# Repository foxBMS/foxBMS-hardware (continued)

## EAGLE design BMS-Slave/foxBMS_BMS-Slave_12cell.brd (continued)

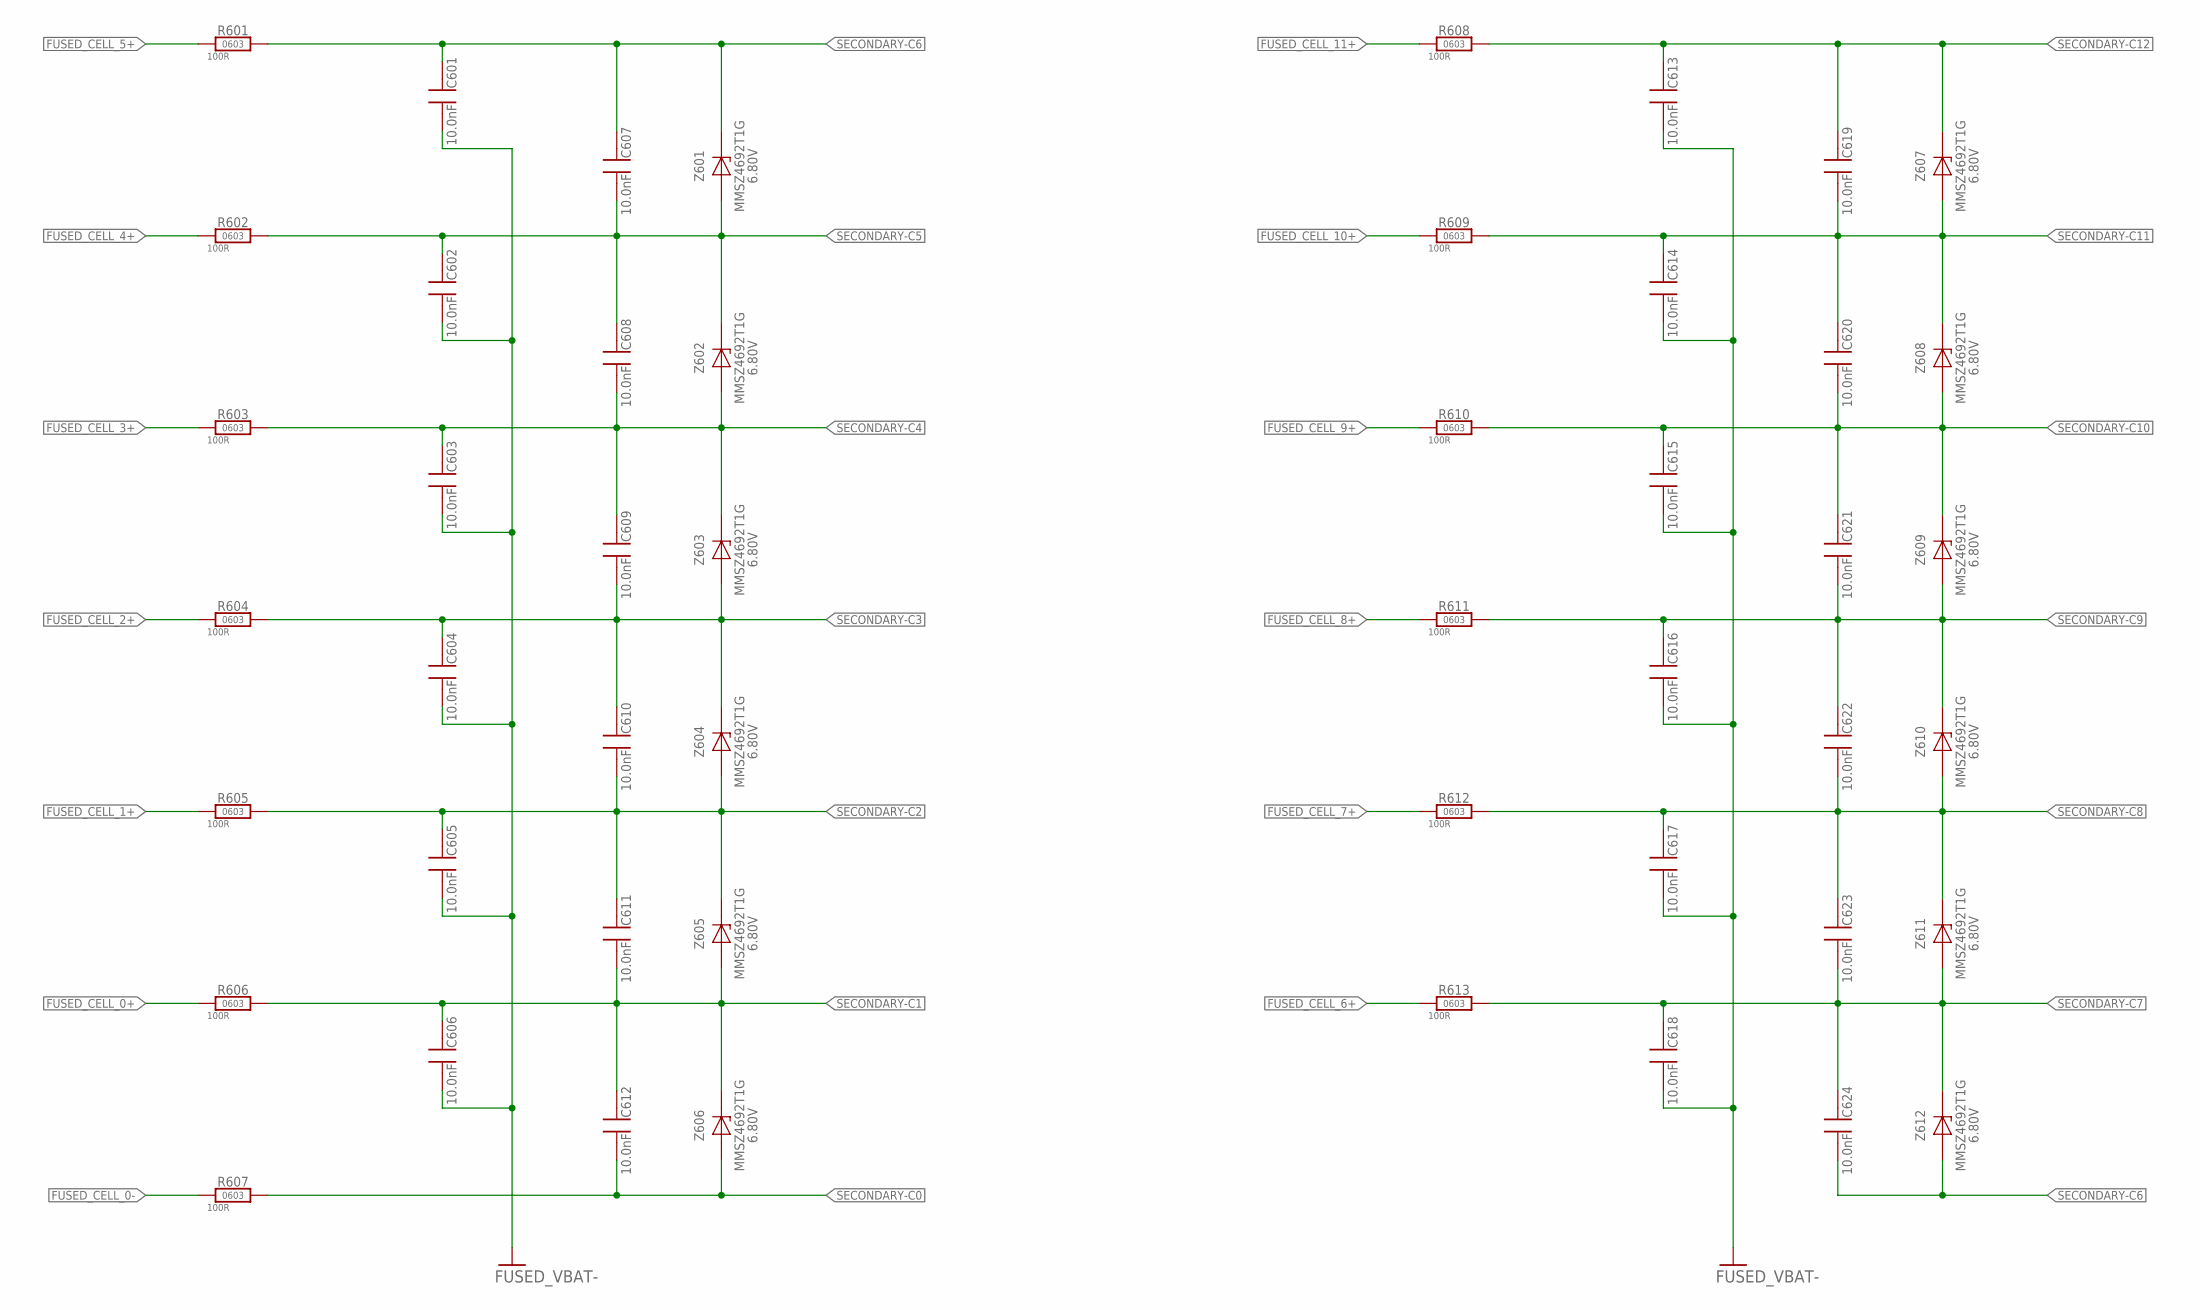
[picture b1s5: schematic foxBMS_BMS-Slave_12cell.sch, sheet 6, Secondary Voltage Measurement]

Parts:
C601, C602, C603, C604, C605, C606, C607, C608, C609, C610, C611, C612, C613, C614, C615, C616, C617, C618, C619, C620, C621, C622, C623, C624: 10nF, 100V, 10%; C_SMD_0603_(1608)_R_KEMET_REV01
R601, R602, R603, R604, R605, R606, R607, R608, R609, R610, R611, R612, R613: 100R_0603_R_VISHAY_1%_TK100_REV_01; R_SMD_0603_R_VISHAY_REV01
Z601, Z602, Z603, Z604, Z605, Z606, Z607, Z608, Z609, Z610, Z611, Z612: 6.8V, 500mW; D_SMD_SOD-123_R_ON_REV01

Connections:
FUSED_CELL_0+: R606.1; also elsewhere on the board
FUSED_CELL_0-: R607.1; also elsewhere on the board
FUSED_CELL_1+: R605.1; also elsewhere on the board
FUSED_CELL_2+: R604.1; also elsewhere on the board
FUSED_CELL_3+: R603.1; also elsewhere on the board
FUSED_CELL_4+: R602.1; also elsewhere on the board
FUSED_CELL_5+: R601.1; also elsewhere on the board
FUSED_CELL_6+: R613.1; also elsewhere on the board
FUSED_CELL_7+: R612.1; also elsewhere on the board
FUSED_CELL_8+: R611.1; also elsewhere on the board
FUSED_CELL_9+: R610.1; also elsewhere on the board
FUSED_CELL_10+: R609.1; also elsewhere on the board
FUSED_CELL_11+: R608.1; also elsewhere on the board
FUSED_VBAT-: C601.2, C602.2, C603.2, C604.2, C605.2, C606.2, C613.2, C614.2, C615.2, C616.2, C617.2, C618.2; also elsewhere on the board
SECONDARY-C0: C612.2, R607.2, Z606.A; also elsewhere on the board
SECONDARY-C1: C606.1, C611.2, C612.1, R606.2, Z605.A, Z606.K (C); also elsewhere on the board
SECONDARY-C2: C605.1, C610.2, C611.1, R605.2, Z604.A, Z605.K (C); also elsewhere on the board
SECONDARY-C3: C604.1, C609.2, C610.1, R604.2, Z603.A, Z604.K (C); also elsewhere on the board
SECONDARY-C4: C603.1, C608.2, C609.1, R603.2, Z602.A, Z603.K (C); also elsewhere on the board
SECONDARY-C5: C602.1, C607.2, C608.1, R602.2, Z601.A, Z602.K (C); also elsewhere on the board
SECONDARY-C6: C601.1, C607.1, C624.2, R601.2, Z601.K (C), Z612.A; also elsewhere on the board
SECONDARY-C7: C618.1, C623.2, C624.1, R613.2, Z611.A, Z612.K (C); also elsewhere on the board
SECONDARY-C8: C617.1, C622.2, C623.1, R612.2, Z610.A, Z611.K (C); also elsewhere on the board
SECONDARY-C9: C616.1, C621.2, C622.1, R611.2, Z609.A, Z610.K (C); also elsewhere on the board
SECONDARY-C10: C615.1, C620.2, C621.1, R610.2, Z608.A, Z609.K (C); also elsewhere on the board
SECONDARY-C11: C614.1, C619.2, C620.1, R609.2, Z607.A, Z608.K (C); also elsewhere on the board
SECONDARY-C12: C613.1, C619.1, R608.2, Z607.K (C); also elsewhere on the board

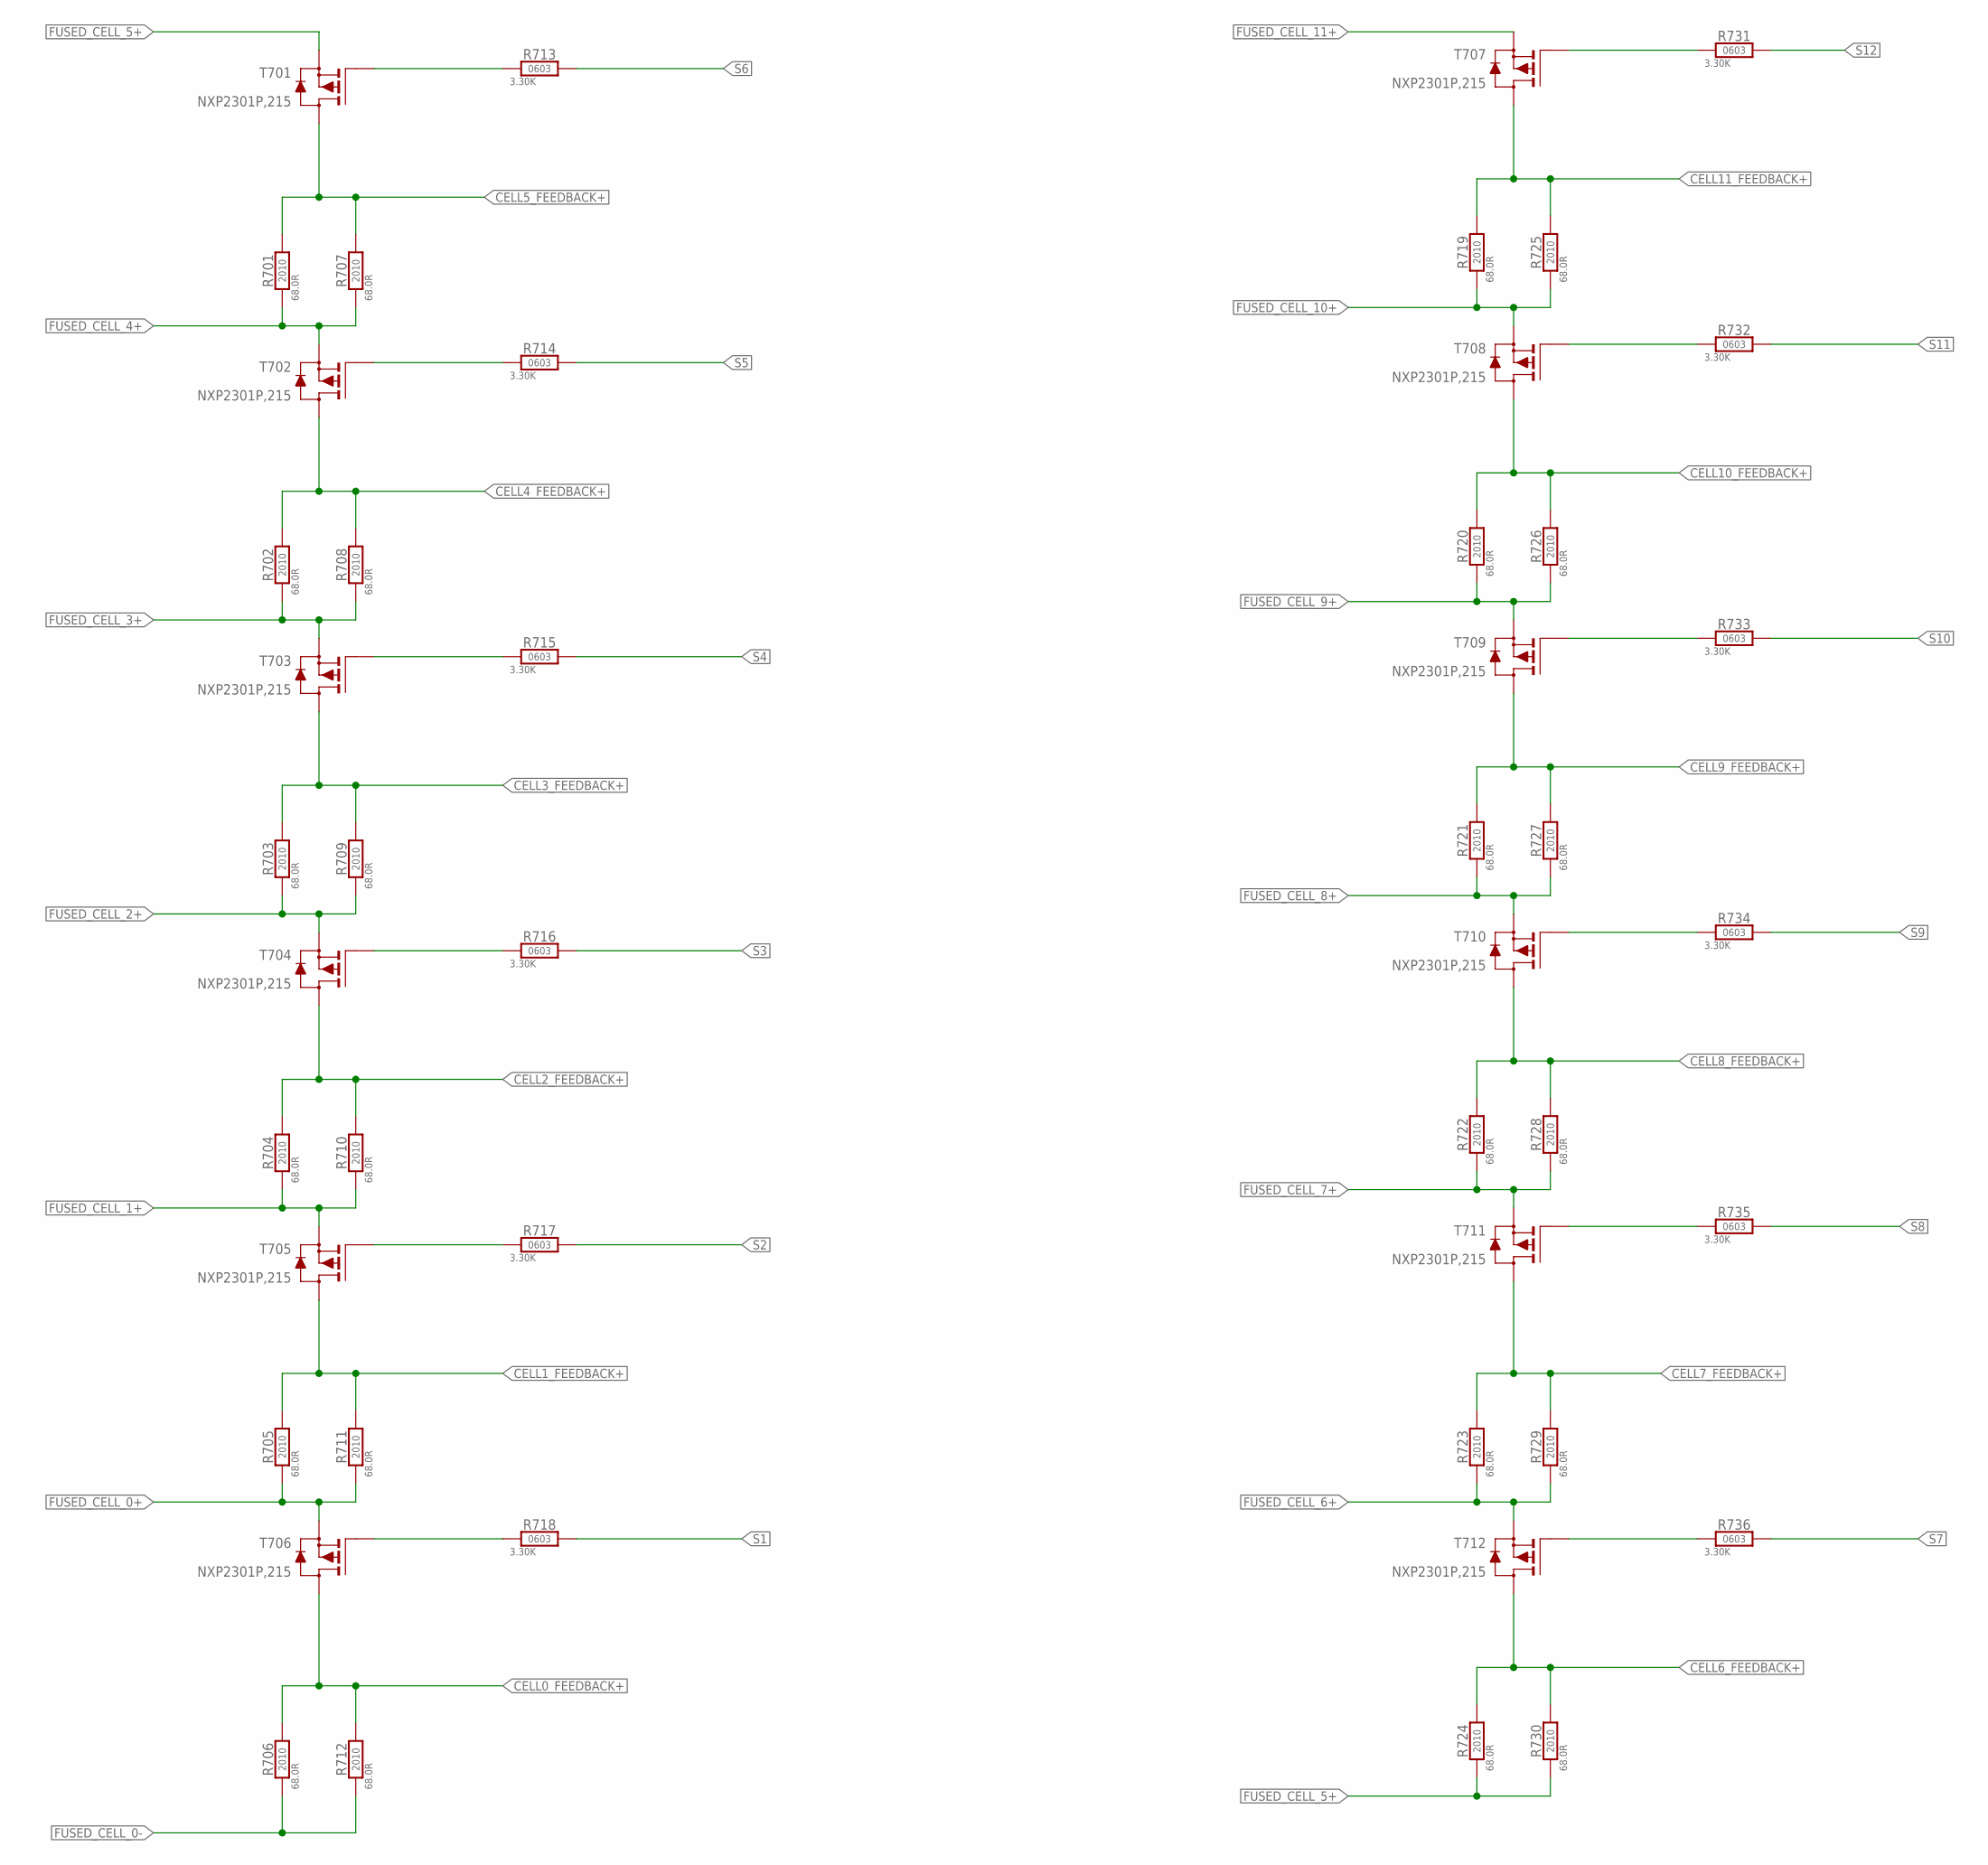
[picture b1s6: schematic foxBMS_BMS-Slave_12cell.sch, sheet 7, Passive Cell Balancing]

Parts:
R701, R702, R703, R704, R705, R706, R707, R708, R709, R710, R711, R712, R719, R720, R721, R722, R723, R724, R725, R726, R727, R728, R729, R730: 72R, 1%; R_SMD_2010_R_YAGEO_REV01
R713, R714, R715, R716, R717, R718, R731, R732, R733, R734, R735, R736: 3.3k, 10%, 1/10W; R_SMD_0603_R_VISHAY_REV01
T701, T702, T703, T704, T705, T706, T707, T708, T709, T710, T711, T712: NX2301P; D_SMD_SOT23_(TO-236AB)_R_NXP_REV01

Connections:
CELL0_FEEDBACK+: R706.P$2 (2), R712.P$2 (2), T706.3 (D); also elsewhere on the board
CELL1_FEEDBACK+: R705.P$2 (2), R711.P$2 (2), T705.3 (D); also elsewhere on the board
CELL2_FEEDBACK+: R704.P$2 (2), R710.P$2 (2), T704.3 (D); also elsewhere on the board
CELL3_FEEDBACK+: R703.P$2 (2), R709.P$2 (2), T703.3 (D); also elsewhere on the board
CELL4_FEEDBACK+: R702.P$2 (2), R708.P$2 (2), T702.3 (D); also elsewhere on the board
CELL5_FEEDBACK+: R701.P$2 (2), R707.P$2 (2), T701.3 (D); also elsewhere on the board
CELL6_FEEDBACK+: R724.P$2 (2), R730.P$2 (2), T712.3 (D); also elsewhere on the board
CELL7_FEEDBACK+: R723.P$2 (2), R729.P$2 (2), T711.3 (D); also elsewhere on the board
CELL8_FEEDBACK+: R722.P$2 (2), R728.P$2 (2), T710.3 (D); also elsewhere on the board
CELL9_FEEDBACK+: R721.P$2 (2), R727.P$2 (2), T709.3 (D); also elsewhere on the board
CELL10_FEEDBACK+: R720.P$2 (2), R726.P$2 (2), T708.3 (D); also elsewhere on the board
CELL11_FEEDBACK+: R719.P$2 (2), R725.P$2 (2), T707.3 (D); also elsewhere on the board
FUSED_CELL_0+: R705.P$1 (1), R711.P$1 (1), T706.2 (S); also elsewhere on the board
FUSED_CELL_0-: R706.P$1 (1), R712.P$1 (1); also elsewhere on the board
FUSED_CELL_1+: R704.P$1 (1), R710.P$1 (1), T705.2 (S); also elsewhere on the board
FUSED_CELL_2+: R703.P$1 (1), R709.P$1 (1), T704.2 (S); also elsewhere on the board
FUSED_CELL_3+: R702.P$1 (1), R708.P$1 (1), T703.2 (S); also elsewhere on the board
FUSED_CELL_4+: R701.P$1 (1), R707.P$1 (1), T702.2 (S); also elsewhere on the board
FUSED_CELL_5+: R724.P$1 (1), R730.P$1 (1), T701.2 (S); also elsewhere on the board
FUSED_CELL_6+: R723.P$1 (1), R729.P$1 (1), T712.2 (S); also elsewhere on the board
FUSED_CELL_7+: R722.P$1 (1), R728.P$1 (1), T711.2 (S); also elsewhere on the board
FUSED_CELL_8+: R721.P$1 (1), R727.P$1 (1), T710.2 (S); also elsewhere on the board
FUSED_CELL_9+: R720.P$1 (1), R726.P$1 (1), T709.2 (S); also elsewhere on the board
FUSED_CELL_10+: R719.P$1 (1), R725.P$1 (1), T708.2 (S); also elsewhere on the board
FUSED_CELL_11+: T707.2 (S); also elsewhere on the board
unnamed: R718.1, T706.1 (G)
unnamed: R717.1, T705.1 (G)
unnamed: R716.1, T704.1 (G)
unnamed: R715.1, T703.1 (G)
unnamed: R714.1, T702.1 (G)
unnamed: R713.1, T701.1 (G)
unnamed: R736.1, T712.1 (G)
unnamed: R735.1, T711.1 (G)
unnamed: R734.1, T710.1 (G)
unnamed: R733.1, T709.1 (G)
unnamed: R732.1, T708.1 (G)
unnamed: R731.1, T707.1 (G)
S1: R718.2; also elsewhere on the board
S2: R717.2; also elsewhere on the board
S3: R716.2; also elsewhere on the board
S4: R715.2; also elsewhere on the board
S5: R714.2; also elsewhere on the board
S6: R713.2; also elsewhere on the board
S7: R736.2; also elsewhere on the board
S8: R735.2; also elsewhere on the board
S9: R734.2; also elsewhere on the board
S10: R733.2; also elsewhere on the board
S11: R732.2; also elsewhere on the board
S12: R731.2; also elsewhere on the board

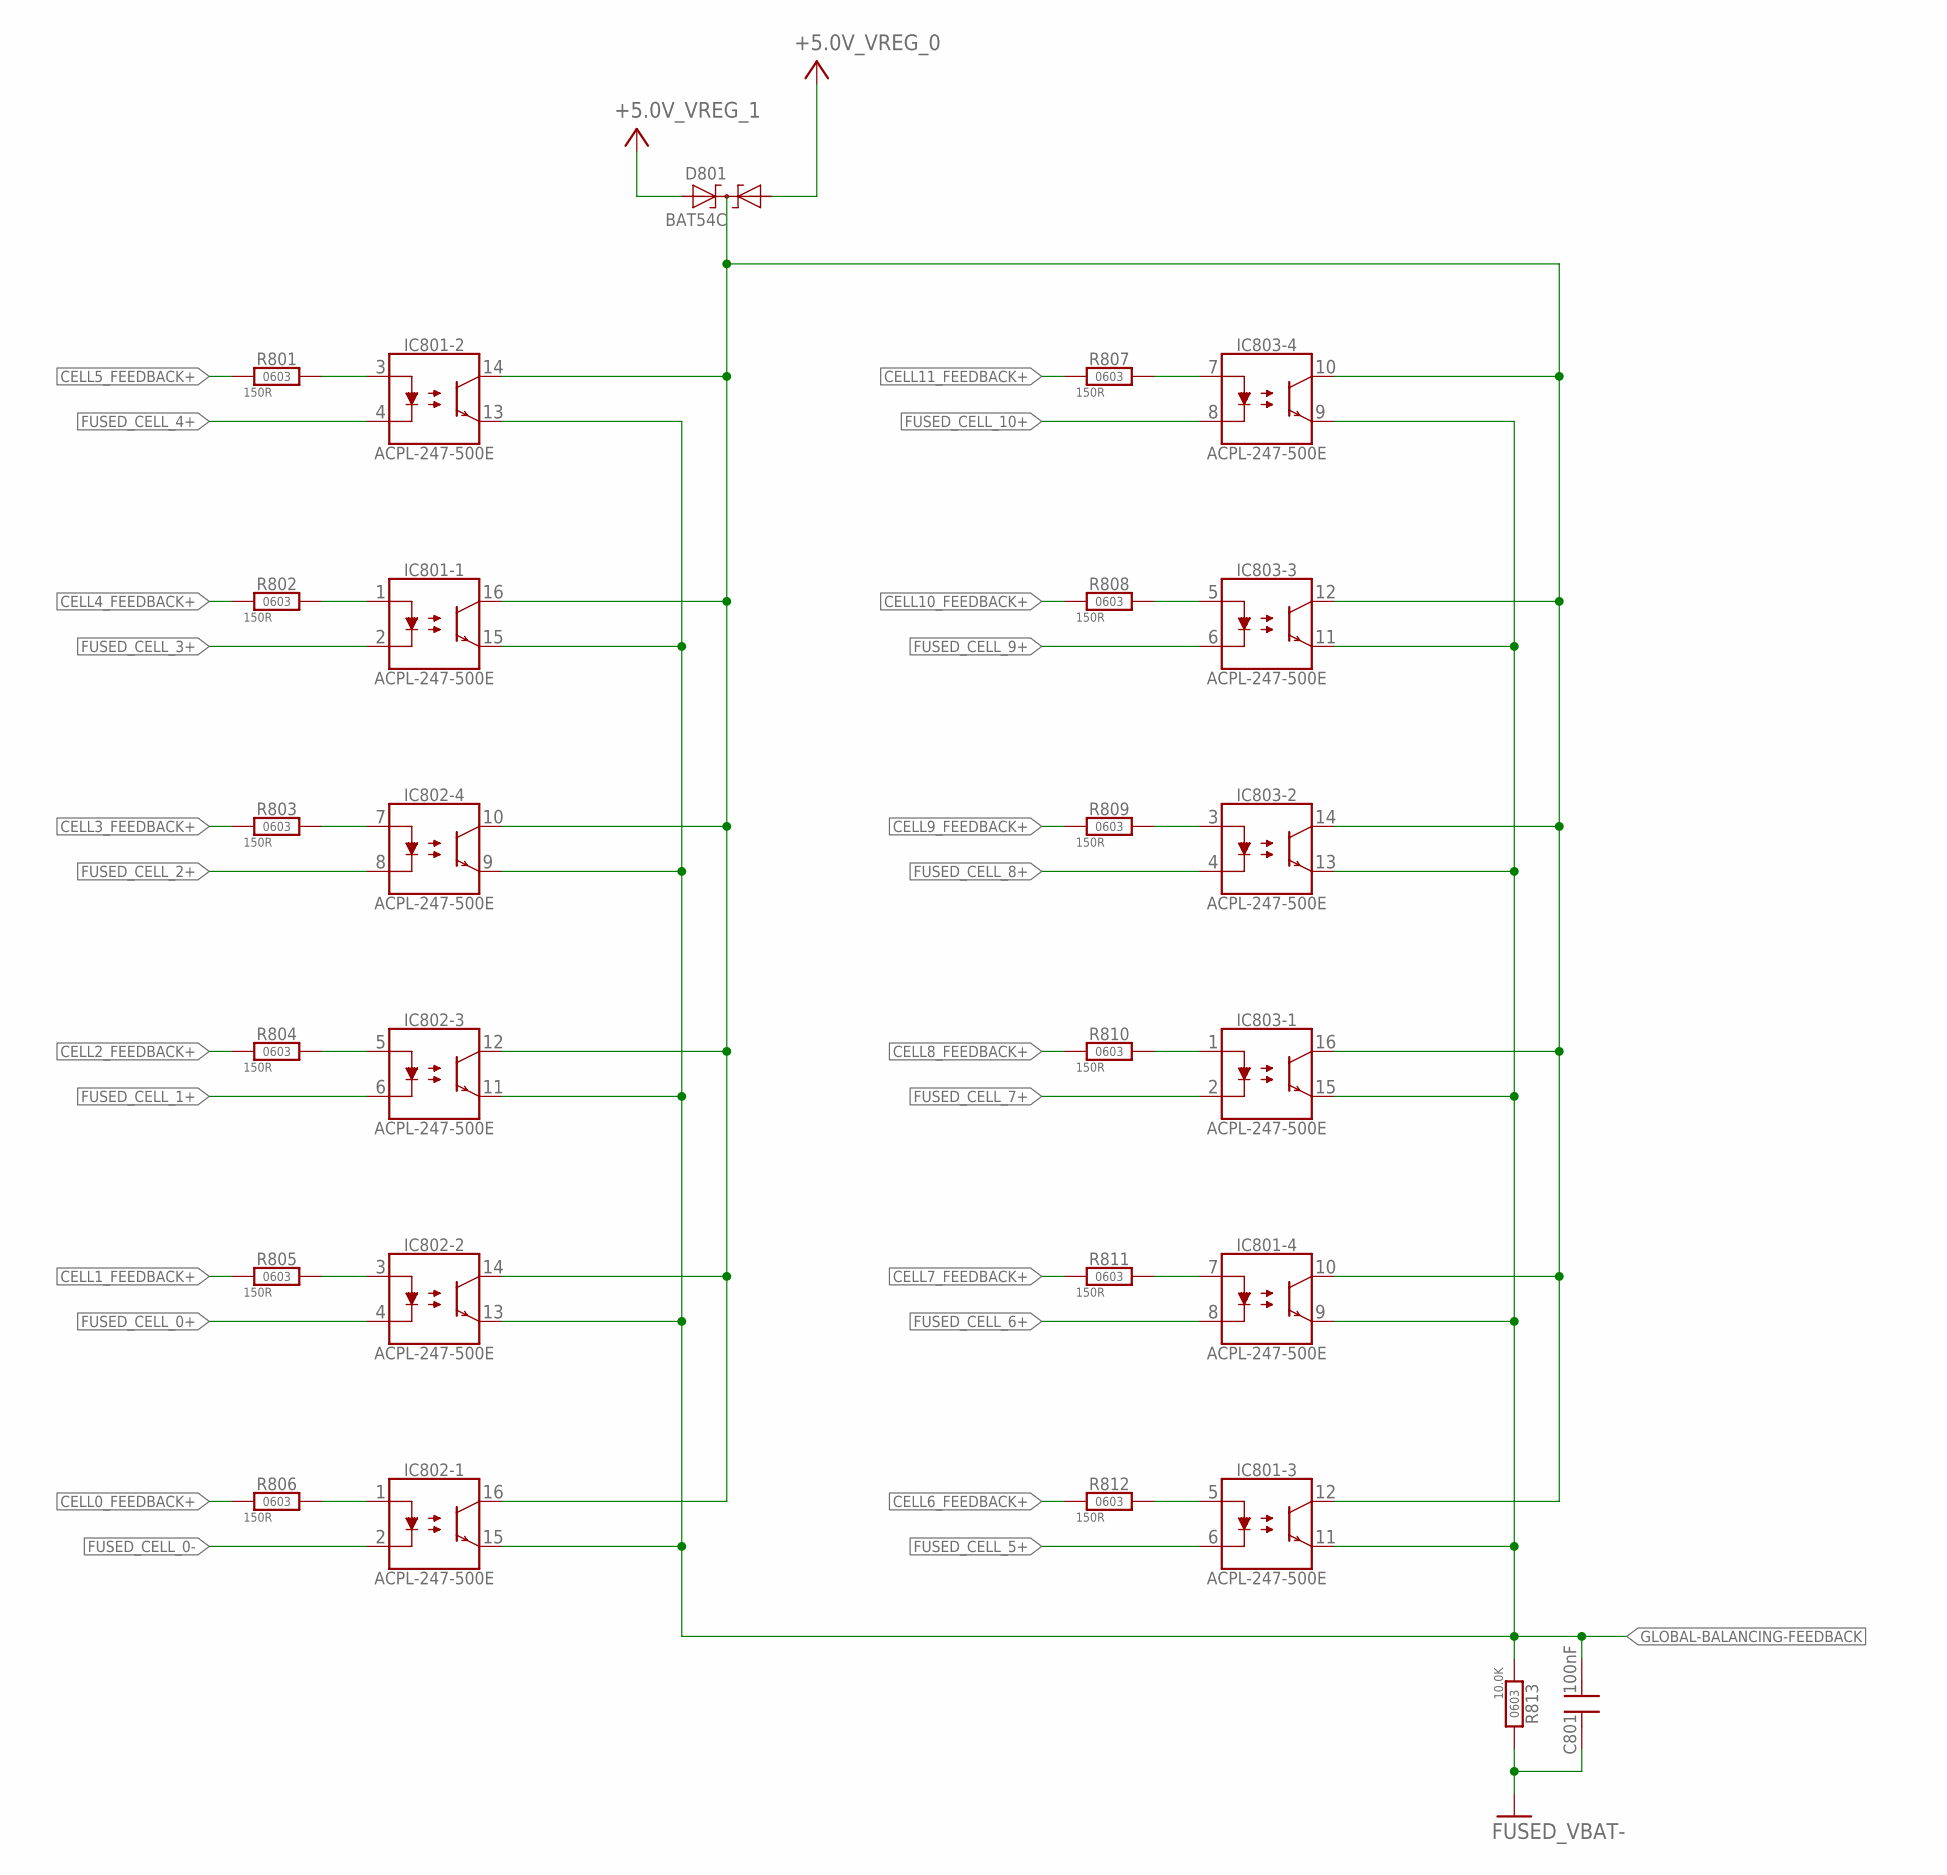
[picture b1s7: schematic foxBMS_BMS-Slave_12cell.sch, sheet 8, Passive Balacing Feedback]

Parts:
C801: 100nF, 20%, 16V; C_SMD_0603_(1608)_R_KEMET_REV01
D801: BAT54C; D_SMD_SOT23_(TO-236AB)_R_NXP_REV01
IC801, IC802, IC803: ACPL-247-500E; OC_SMD_SOIC-16_R_AVAGO_REV01
R801, R802, R803, R804, R805, R806, R807, R808, R809, R810, R811, R812: 150R_0603_R_VISHAY_1%_TK100_REV_01; R_SMD_0603_R_VISHAY_REV01
R813: 10,0K_0603_R_VISHAY_1%_TK100_REV_01; R_SMD_0603_R_VISHAY_REV01

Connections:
+5.0V_VREG_0: D801.2 (A2); also elsewhere on the board
+5.0V_VREG_1: D801.1 (A1); also elsewhere on the board
CELL0_FEEDBACK+: R806.1; also elsewhere on the board
CELL1_FEEDBACK+: R805.1; also elsewhere on the board
CELL2_FEEDBACK+: R804.1; also elsewhere on the board
CELL3_FEEDBACK+: R803.1; also elsewhere on the board
CELL4_FEEDBACK+: R802.1; also elsewhere on the board
CELL5_FEEDBACK+: R801.1; also elsewhere on the board
CELL6_FEEDBACK+: R812.1; also elsewhere on the board
CELL7_FEEDBACK+: R811.1; also elsewhere on the board
CELL8_FEEDBACK+: R810.1; also elsewhere on the board
CELL9_FEEDBACK+: R809.1; also elsewhere on the board
CELL10_FEEDBACK+: R808.1; also elsewhere on the board
CELL11_FEEDBACK+: R807.1; also elsewhere on the board
FUSED_CELL_0+: IC802.4 (K); also elsewhere on the board
FUSED_CELL_0-: IC802.2 (K); also elsewhere on the board
FUSED_CELL_1+: IC802.6 (K); also elsewhere on the board
FUSED_CELL_2+: IC802.8 (K); also elsewhere on the board
FUSED_CELL_3+: IC801.2 (K); also elsewhere on the board
FUSED_CELL_4+: IC801.4 (K); also elsewhere on the board
FUSED_CELL_5+: IC801.6 (K); also elsewhere on the board
FUSED_CELL_6+: IC801.8 (K); also elsewhere on the board
FUSED_CELL_7+: IC803.2 (K); also elsewhere on the board
FUSED_CELL_8+: IC803.4 (K); also elsewhere on the board
FUSED_CELL_9+: IC803.6 (K); also elsewhere on the board
FUSED_CELL_10+: IC803.8 (K); also elsewhere on the board
FUSED_VBAT-: C801.1, R813.2; also elsewhere on the board
GLOBAL-BALANCING-FEEDBACK: C801.2, IC801.9 (V_EMITTER), IC801.11 (V_EMITTER), IC801.13 (V_EMITTER), IC801.15 (V_EMITTER), IC802.9 (V_EMITTER), IC802.11 (V_EMITTER), IC802.13 (V_EMITTER), IC802.15 (V_EMITTER), IC803.9 (V_EMITTER), IC803.11 (V_EMITTER), IC803.13 (V_EMITTER), IC803.15 (V_EMITTER), R813.1; also elsewhere on the board
unnamed: D801.3 (C), IC801.10 (V_COLLECTOR), IC801.12 (V_COLLECTOR), IC801.14 (V_COLLECTOR), IC801.16 (V_COLLECTOR), IC802.10 (V_COLLECTOR), IC802.12 (V_COLLECTOR), IC802.14 (V_COLLECTOR), IC802.16 (V_COLLECTOR), IC803.10 (V_COLLECTOR), IC803.12 (V_COLLECTOR), IC803.14 (V_COLLECTOR), IC803.16 (V_COLLECTOR)
unnamed: IC801.1 (A), R802.2
unnamed: IC802.7 (A), R803.2
unnamed: IC802.5 (A), R804.2
unnamed: IC803.5 (A), R808.2
unnamed: IC803.3 (A), R809.2
unnamed: IC802.3 (A), R805.2
unnamed: IC803.7 (A), R807.2
unnamed: IC803.1 (A), R810.2
unnamed: IC801.7 (A), R811.2
unnamed: IC802.1 (A), R806.2
unnamed: IC801.5 (A), R812.2
unnamed: IC801.3 (A), R801.2

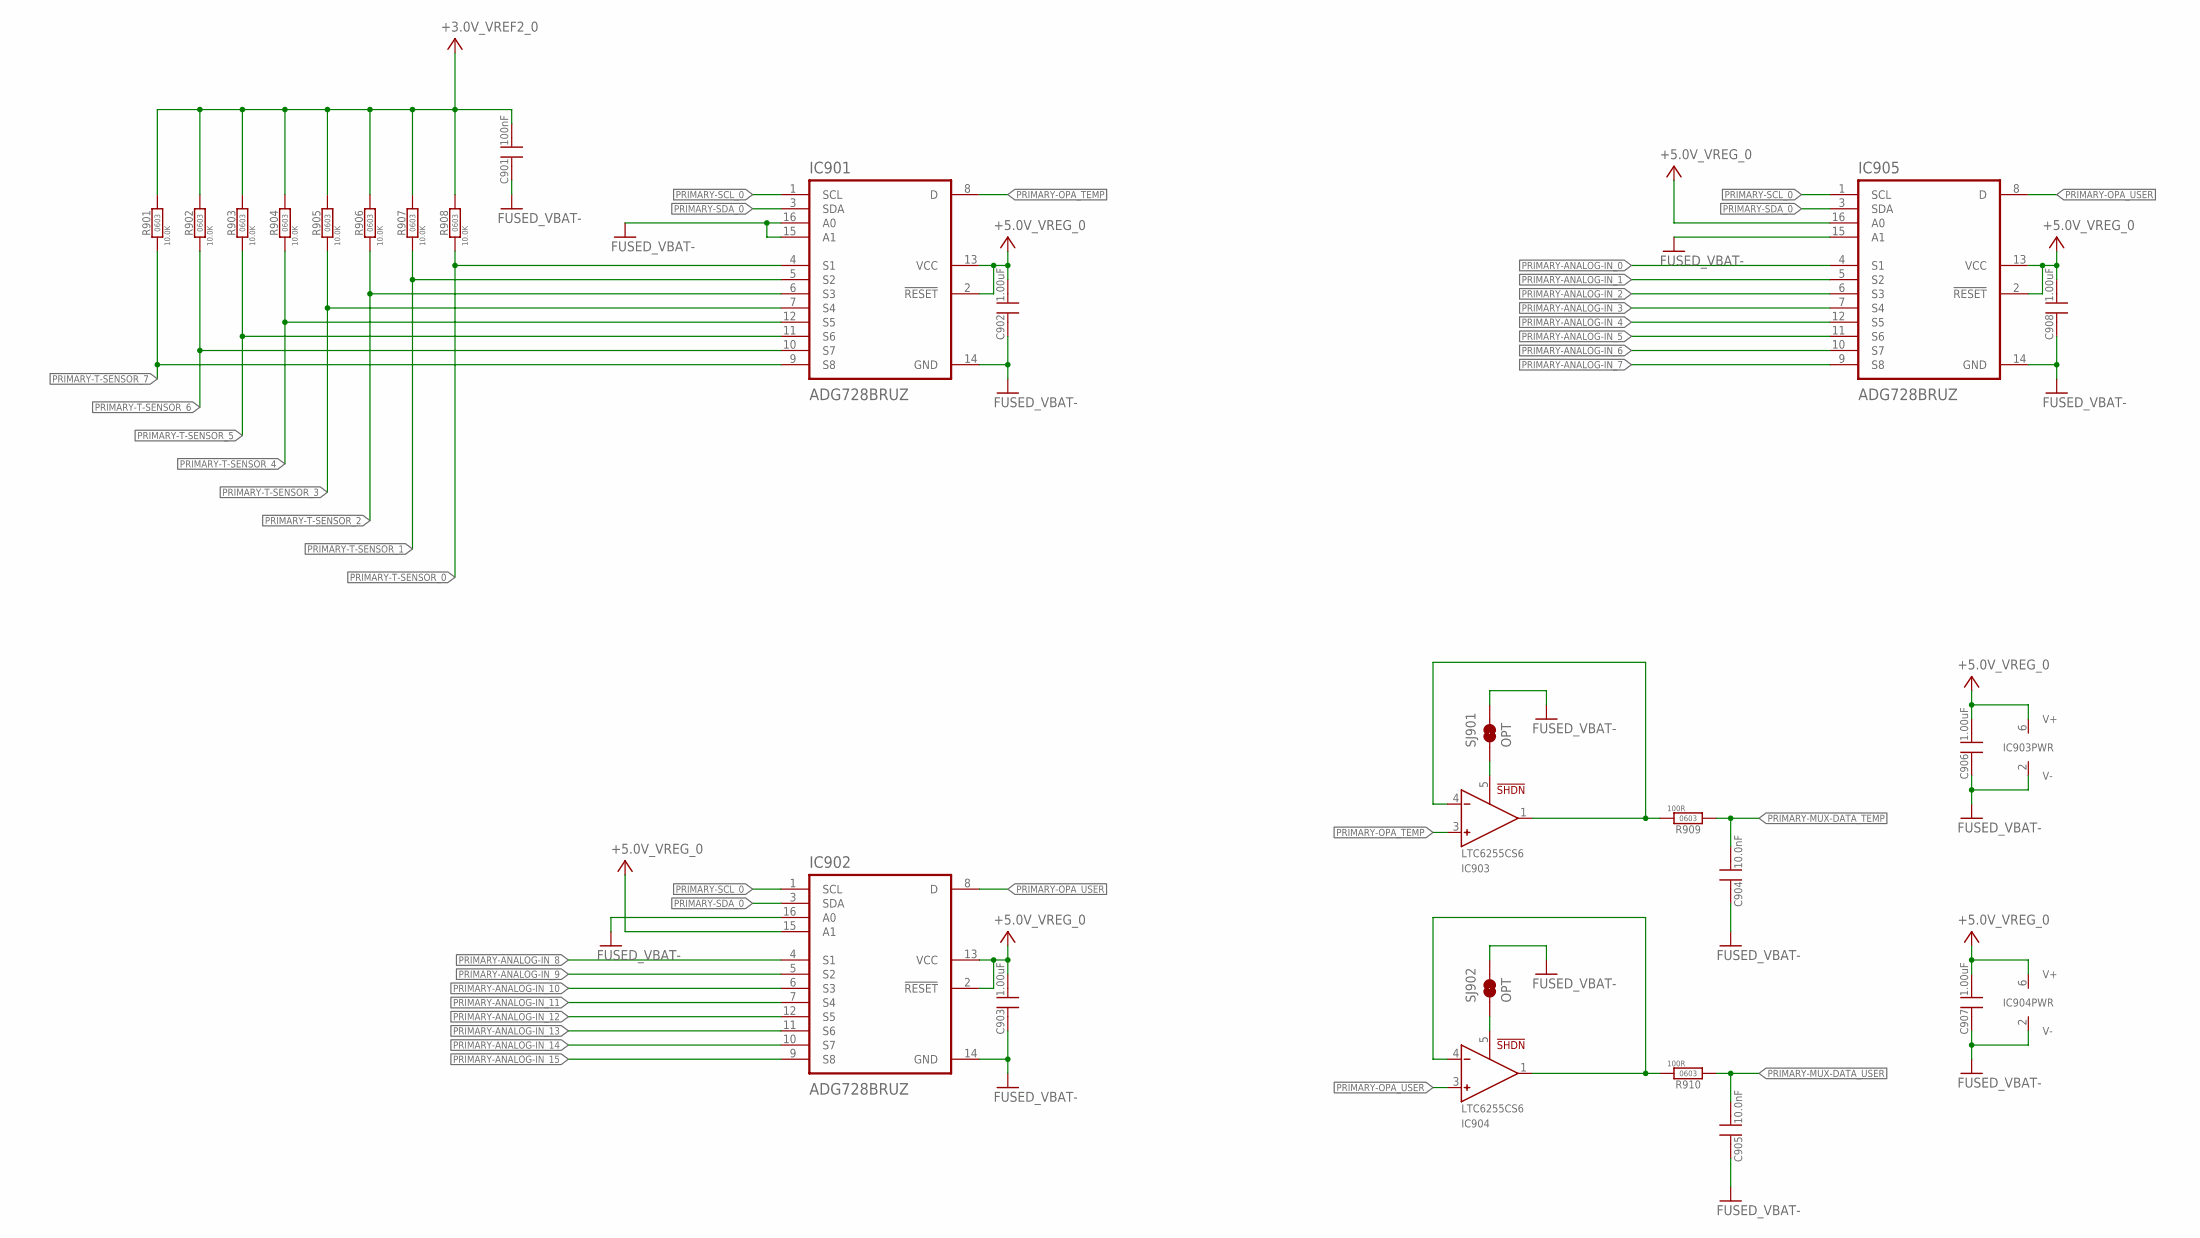
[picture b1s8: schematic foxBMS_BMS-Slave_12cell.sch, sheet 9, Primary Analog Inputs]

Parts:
C901: 100nF, 20%, 16V; C_SMD_0603_(1608)_R_KEMET_REV01
C902, C903, C906, C907, C908: 1uF, 20%, 16V; C_SMD_0603_(1608)_R_KEMET_REV01
C904, C905: 10nF, 100V, 10%; C_SMD_0603_(1608)_R_KEMET_REV01
IC901, IC902, IC905: ADG728BRUZ; SOP65P638X110-16N
IC903, IC904: LTC6255CS6; IC_SMD_TSOT-23-6_(S6)_R_LINEAR_REV01
R901, R902, R903, R904, R905, R906, R907, R908: 10,0K_0603_R_VISHAY_1%_TK100_REV_01; R_SMD_0603_R_VISHAY_REV01
R909, R910: 100R_0603_R_VISHAY_1%_TK100_REV_01; R_SMD_0603_R_VISHAY_REV01
SJ901, SJ902: OPT; CUSTOM_JUMPER_SJ

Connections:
+3.0V_VREF2_0: C901.2, R901.2, R902.2, R903.2, R904.2, R905.2, R906.2, R907.2, R908.2; also elsewhere on the board
+5.0V_VREG_0: C902.2, C903.2, C906.2, C907.2, C908.2, IC901.2 (!RESET), IC901.13 (VCC), IC902.2 (!RESET), IC902.13 (VCC), IC902.15 (A1), IC903.6 (V+), IC904.6 (V+), IC905.2 (!RESET), IC905.13 (VCC), IC905.16 (A0); also elsewhere on the board
FUSED_VBAT-: C901.1, C902.1, C903.1, C904.1, C905.1, C906.1, C907.1, C908.1, IC901.14 (GND), IC901.15 (A1), IC901.16 (A0), IC902.14 (GND), IC902.16 (A0), IC903.2 (V-), IC904.2 (V-), IC905.14 (GND), IC905.15 (A1), SJ901.2, SJ902.2; also elsewhere on the board
unnamed: IC904.1 (VOUT), IC904.4 (-), R910.1
unnamed: IC904.5 (!SHDN), SJ902.1
unnamed: IC903.1 (VOUT), IC903.4 (-), R909.1
unnamed: IC903.5 (!SHDN), SJ901.1
PRIMARY-ANALOG-IN_0: IC905.4 (S1); also elsewhere on the board
PRIMARY-ANALOG-IN_1: IC905.5 (S2); also elsewhere on the board
PRIMARY-ANALOG-IN_2: IC905.6 (S3); also elsewhere on the board
PRIMARY-ANALOG-IN_3: IC905.7 (S4); also elsewhere on the board
PRIMARY-ANALOG-IN_4: IC905.12 (S5); also elsewhere on the board
PRIMARY-ANALOG-IN_5: IC905.11 (S6); also elsewhere on the board
PRIMARY-ANALOG-IN_6: IC905.10 (S7); also elsewhere on the board
PRIMARY-ANALOG-IN_7: IC905.9 (S8); also elsewhere on the board
PRIMARY-ANALOG-IN_8: IC902.4 (S1); also elsewhere on the board
PRIMARY-ANALOG-IN_9: IC902.5 (S2); also elsewhere on the board
PRIMARY-ANALOG-IN_10: IC902.6 (S3); also elsewhere on the board
PRIMARY-ANALOG-IN_11: IC902.7 (S4); also elsewhere on the board
PRIMARY-ANALOG-IN_12: IC902.12 (S5); also elsewhere on the board
PRIMARY-ANALOG-IN_13: IC902.11 (S6); also elsewhere on the board
PRIMARY-ANALOG-IN_14: IC902.10 (S7); also elsewhere on the board
PRIMARY-ANALOG-IN_15: IC902.9 (S8); also elsewhere on the board
PRIMARY-MUX-DATA_TEMP: C904.2, R909.2; also elsewhere on the board
PRIMARY-MUX-DATA_USER: C905.2, R910.2; also elsewhere on the board
PRIMARY-OPA_TEMP: IC901.8 (D), IC903.3 (+)
PRIMARY-OPA_USER: IC902.8 (D), IC904.3 (+), IC905.8 (D)
PRIMARY-SCL_0: IC901.1 (SCL), IC902.1 (SCL), IC905.1 (SCL); also elsewhere on the board
PRIMARY-SDA_0: IC901.3 (SDA), IC902.3 (SDA), IC905.3 (SDA); also elsewhere on the board
PRIMARY-T-SENSOR_0: IC901.4 (S1), R908.1; also elsewhere on the board
PRIMARY-T-SENSOR_1: IC901.5 (S2), R907.1; also elsewhere on the board
PRIMARY-T-SENSOR_2: IC901.6 (S3), R906.1; also elsewhere on the board
PRIMARY-T-SENSOR_3: IC901.7 (S4), R905.1; also elsewhere on the board
PRIMARY-T-SENSOR_4: IC901.12 (S5), R904.1; also elsewhere on the board
PRIMARY-T-SENSOR_5: IC901.11 (S6), R903.1; also elsewhere on the board
PRIMARY-T-SENSOR_6: IC901.10 (S7), R902.1; also elsewhere on the board
PRIMARY-T-SENSOR_7: IC901.9 (S8), R901.1; also elsewhere on the board
